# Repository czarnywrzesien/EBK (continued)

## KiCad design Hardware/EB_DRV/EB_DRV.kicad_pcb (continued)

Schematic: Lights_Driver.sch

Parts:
C18, C21, C22, C25, C26, C27: 100n; C_0805_HandSoldering
C19, C20: 20p; C_0805_HandSoldering
C23, C24: C; C_0805_HandSoldering
C28: 4,7u; C_0805_HandSoldering
P8: CONN_01X03; Pin_Header_Straight_1x03
R4, R22: 100; R_0805_HandSoldering
R19: 100k; R_0805_HandSoldering
R20, R21: 330; R_0805_HandSoldering
R23, R24: 220k; R_0805_HandSoldering
SW1: SW_PUSH; SW_SPST_B3S-1000
U3: STM32F100RBT6; TQFP-64_10x10mm_Pitch0.5mm
Y2: Crystal_Small; Crystal_HC18-U_Vertical

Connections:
/Light_sensor/L_SIGNAL: U3.8 (PC0); also elsewhere on the board
/Lights/K1_IN: U3.9 (PC1); also elsewhere on the board
/Lights/K2_IN: U3.10 (PC2); also elsewhere on the board
/Lights/K3_IN: U3.11 (PC3); also elsewhere on the board
/Lights/K4_IN: U3.24 (PC4); also elsewhere on the board
/Lights/K5_IN: U3.25 (PC5); also elsewhere on the board
/Lights/K6_IN: U3.37 (PC6); also elsewhere on the board
/Lights/K7_IN: U3.38 (PC7); also elsewhere on the board
/Lights/K8_IN: U3.39 (PC8); also elsewhere on the board
/Lights/TAB1_IN: U3.51 (PC10); also elsewhere on the board
/Lights/TAB2_IN: U3.52 (PC11); also elsewhere on the board
/Lights/W1_IN: U3.20 (PA4); also elsewhere on the board
/Lights/W2_IN: U3.21 (PA5); also elsewhere on the board
/Lights/W3_IN: U3.22 (PA6); also elsewhere on the board
/Lights/W4_IN: U3.23 (PA7); also elsewhere on the board
/Lights/W5_IN: U3.41 (PA8); also elsewhere on the board
/Lights/W6_IN: U3.42 (PA9); also elsewhere on the board
/Lights/W7_IN: U3.43 (PA10); also elsewhere on the board
/Lights/W8_IN: U3.44 (PA11); also elsewhere on the board
/Lights_driver/ALL_L_IN: U3.57 (PB5); also elsewhere on the board
/Lights_driver/DEBUG_RX: U3.17 (PA3); also elsewhere on the board
/Lights_driver/DEBUG_TX: U3.16 (PA2); also elsewhere on the board
/Lights_driver/LED_L: U3.58 (PB6); also elsewhere on the board
/Lights_driver/LED_R: U3.59 (PB7); also elsewhere on the board
/Lights_driver/L_L_IN: U3.56 (PB4); also elsewhere on the board
/Lights_driver/R_L_IN: U3.55 (PB3); also elsewhere on the board
/Lights_driver/ST_RESET2: C18.1, R19.1, SW1.1, U3.7 (NRST); also elsewhere on the board
/Lights_driver/ST_SWCLK2: U3.49 (PA14); also elsewhere on the board
/Lights_driver/ST_SWDIO2: U3.46 (PA13); also elsewhere on the board
/Lights_driver/WHL_FR: U3.53 (PC12); also elsewhere on the board
/Lights_driver/WHL_RE: U3.54 (PD2); also elsewhere on the board
/MCU/I2C_DATA: U3.30 (PB11); also elsewhere on the board
/MCU/I2C_SCK: U3.29 (PB10); also elsewhere on the board
unnamed: C19.2, U3.6 (PD1-OSC_OUT), Y2.1
unnamed: C20.2, U3.5 (PD0_OSC_IN), Y2.2
unnamed: C23.1, R22.2
unnamed: C23.2, P8.2, R21.1, R23.1
unnamed: C24.1, R4.1
unnamed: C24.2, P8.3, R20.1, R24.1
unnamed: R20.2, U3.33 (PB12)
unnamed: R21.2, U3.34 (PB13)

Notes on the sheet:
Autor: Krzysztof Piechowski Praca Magisterska Kontroler oswietlenia
Sterownik eBike

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
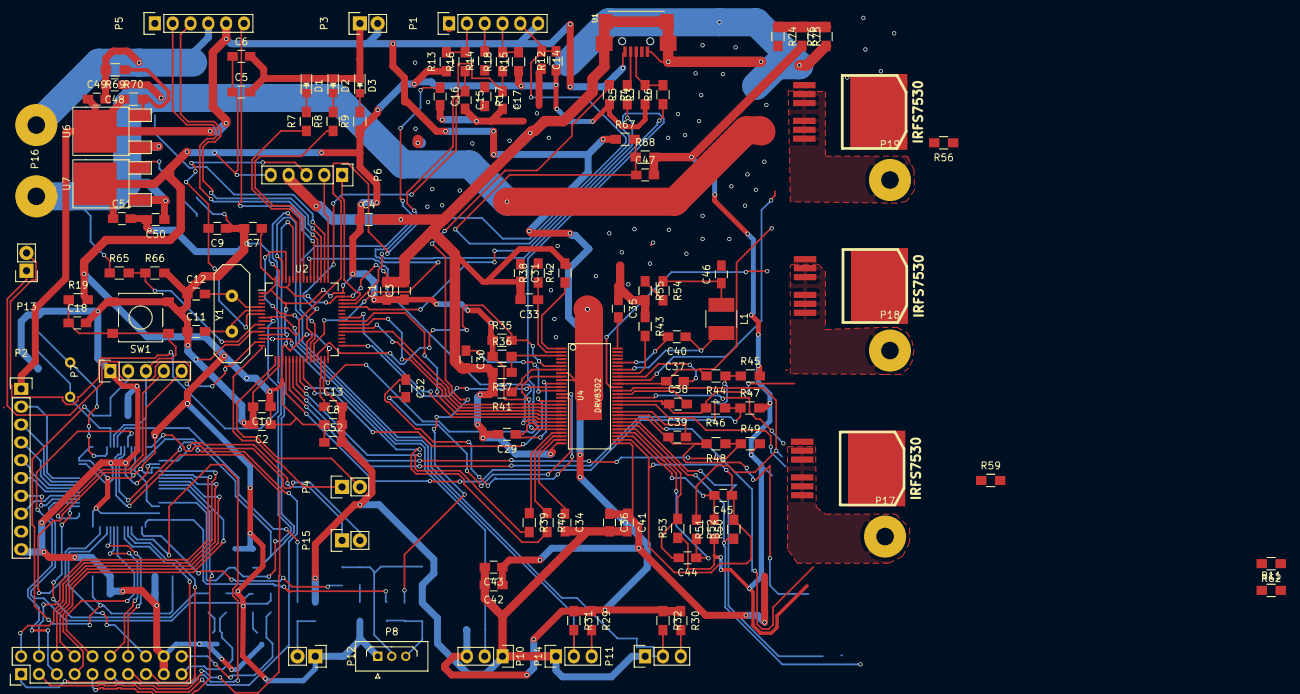
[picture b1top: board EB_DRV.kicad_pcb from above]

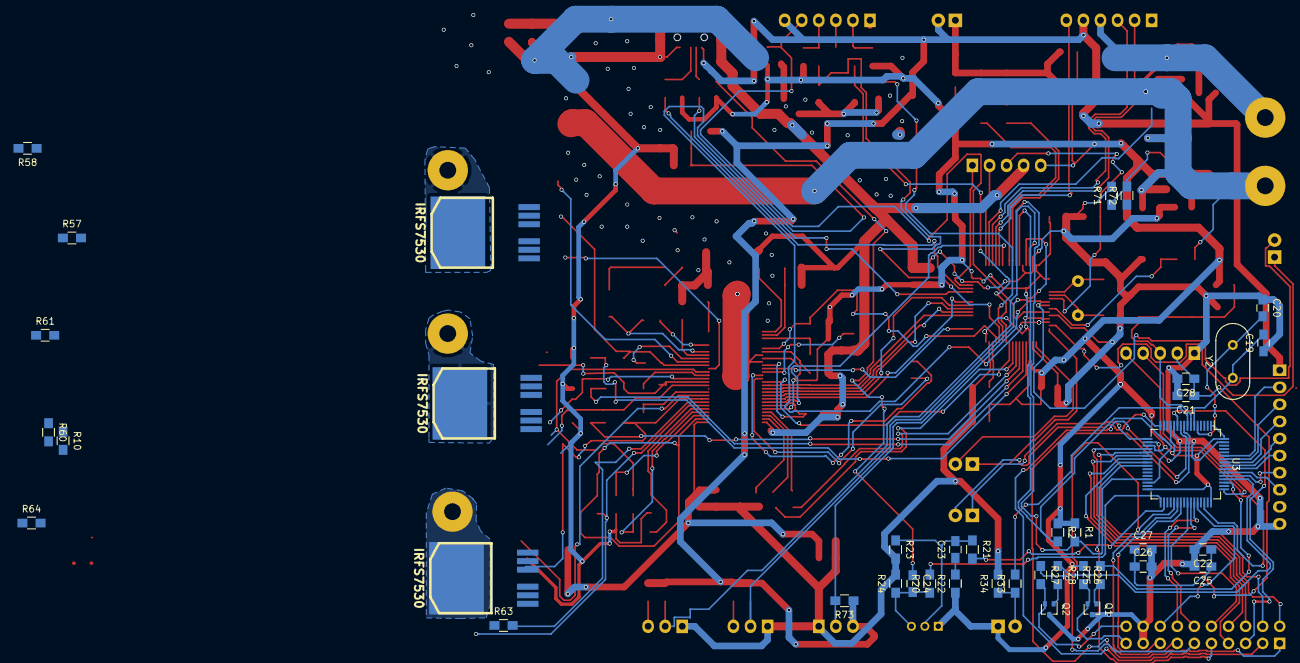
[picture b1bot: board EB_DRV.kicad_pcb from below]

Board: 2 copper layers, 168 parts (40 on the bottom side), 148 nets.

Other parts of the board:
P12: PhotoRes_CONN; Pin_Header_Straight_1x02
P13: CONN_01X02; Pin_Header_Straight_1x02
Q3, Q4, Q5, Q6, Q7, Q8: IRFS7530; D2PAK-7-GDS
R33: 220; R_0805_HandSoldering
R34: 2k; R_0805_HandSoldering
R56, R57, R59, R60, R62, R63: 4R7; R_0805_HandSoldering
R58, R61, R64: 39k; R_0805_HandSoldering
R65: 100k; R_0805_HandSoldering
R66: 10k; R_0805_HandSoldering

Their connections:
+36V: Q3.D, Q5.D, Q7.D, R65.1; also elsewhere on the board
/Batterry_Measurment/BAT_CURR_A: P13.2; also elsewhere on the board
/Batterry_Measurment/BAT_CURR_B: P13.1; also elsewhere on the board
/Batterry_Measurment/BAT_VOL: R65.2, R66.1; also elsewhere on the board
/Light_sensor/L_SIGNAL: R33.2; also elsewhere on the board
/MOSFET_PWR/H1_LOW: Q4.S, R58.1, R61.2; also elsewhere on the board
/MOSFET_PWR/H1_VS: Q3.S, Q4.D; also elsewhere on the board
/MOSFET_PWR/H2_VS: Q5.S, Q6.D; also elsewhere on the board
/MOSFET_PWR/H3_LOW: Q8.S, R64.2; also elsewhere on the board
/MOSFET_PWR/H3_VS: Q7.S, Q8.D; also elsewhere on the board
/MOSFET_PWR/M_H1: R56.2; also elsewhere on the board
/MOSFET_PWR/M_H2: R59.2; also elsewhere on the board
/MOSFET_PWR/M_H3: R62.2; also elsewhere on the board
/MOSFET_PWR/M_L1: R57.2; also elsewhere on the board
/MOSFET_PWR/M_L2: R60.2; also elsewhere on the board
/MOSFET_PWR/M_L3: R63.2; also elsewhere on the board
unnamed: P12.2, R33.1, R34.1
unnamed: Q3.G, R56.1
unnamed: Q4.G, R57.1, R58.2
unnamed: Q5.G, R59.1
unnamed: Q6.G, R60.1, R61.1
unnamed: Q7.G, R62.1
unnamed: Q8.G, R63.1, R64.1

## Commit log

2017-03-27 New folder structure
